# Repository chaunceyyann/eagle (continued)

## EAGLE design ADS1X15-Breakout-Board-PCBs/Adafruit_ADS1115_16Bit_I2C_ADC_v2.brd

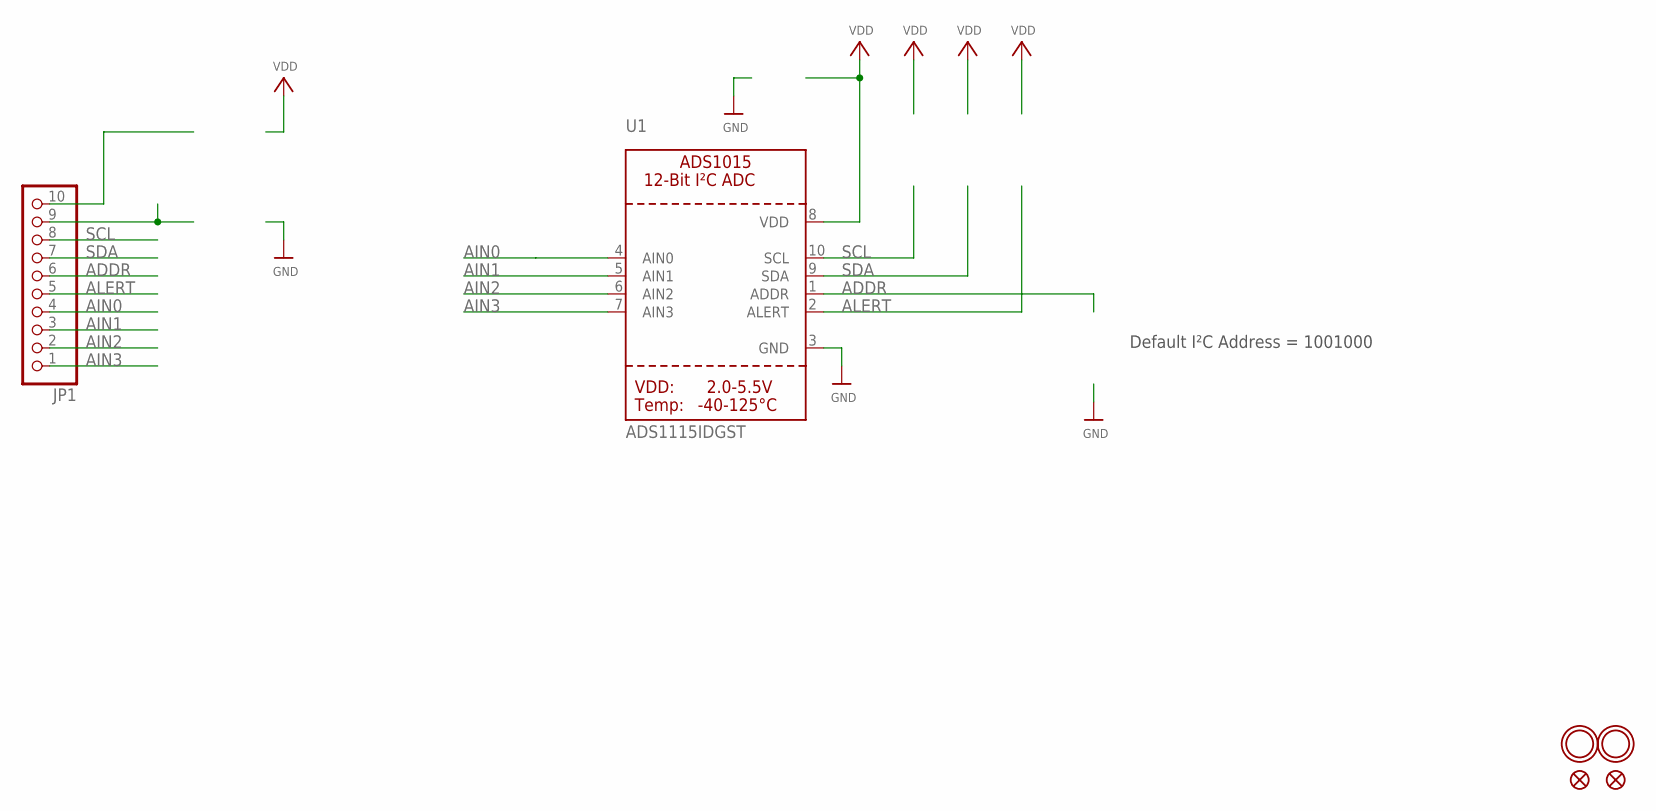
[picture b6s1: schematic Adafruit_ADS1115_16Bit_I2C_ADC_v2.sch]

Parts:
FID1, FID2: FIDUCIAL""; FIDUCIAL_1MM
JP1: HEADER-1X1070MIL; 1X10_ROUND70
U1: ADS1115IDGST; MSOP10
U$13, U$14: MOUNTINGHOLE2.5; MOUNTINGHOLE_2.5_PLATED

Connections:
ADDR: JP1.6, U1.1 (ADDR)
AIN0: JP1.4, U1.4 (AIN0)
AIN1: JP1.3, U1.5 (AIN1)
AIN2: JP1.2, U1.6 (AIN2)
AIN3: JP1.1, U1.7 (AIN3)
ALERT: JP1.5, U1.2 (ALERT)
GND: U1.3 (GND)
SCL: JP1.8, U1.10 (SCL)
SDA: JP1.7, U1.9 (SDA)
VDD: U1.8 (VDD)

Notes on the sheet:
Default I²C Address = 1001000

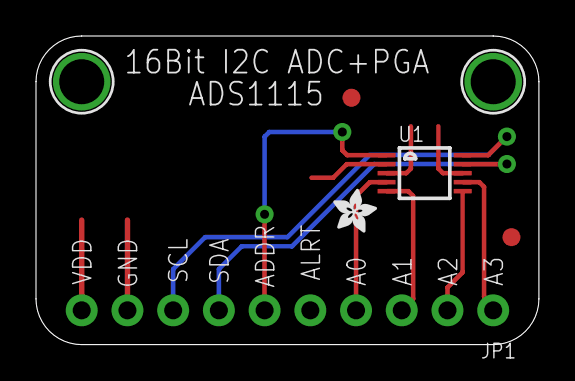
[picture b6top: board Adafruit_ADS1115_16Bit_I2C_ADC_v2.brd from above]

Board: 2 copper layers, 27.9 x 17.1 mm, 8 parts (1 on the bottom side), 8 nets.

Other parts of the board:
U$15: ADAFRUIT_TEXT_20MM
U$16: ADAFRUIT_2.5MM

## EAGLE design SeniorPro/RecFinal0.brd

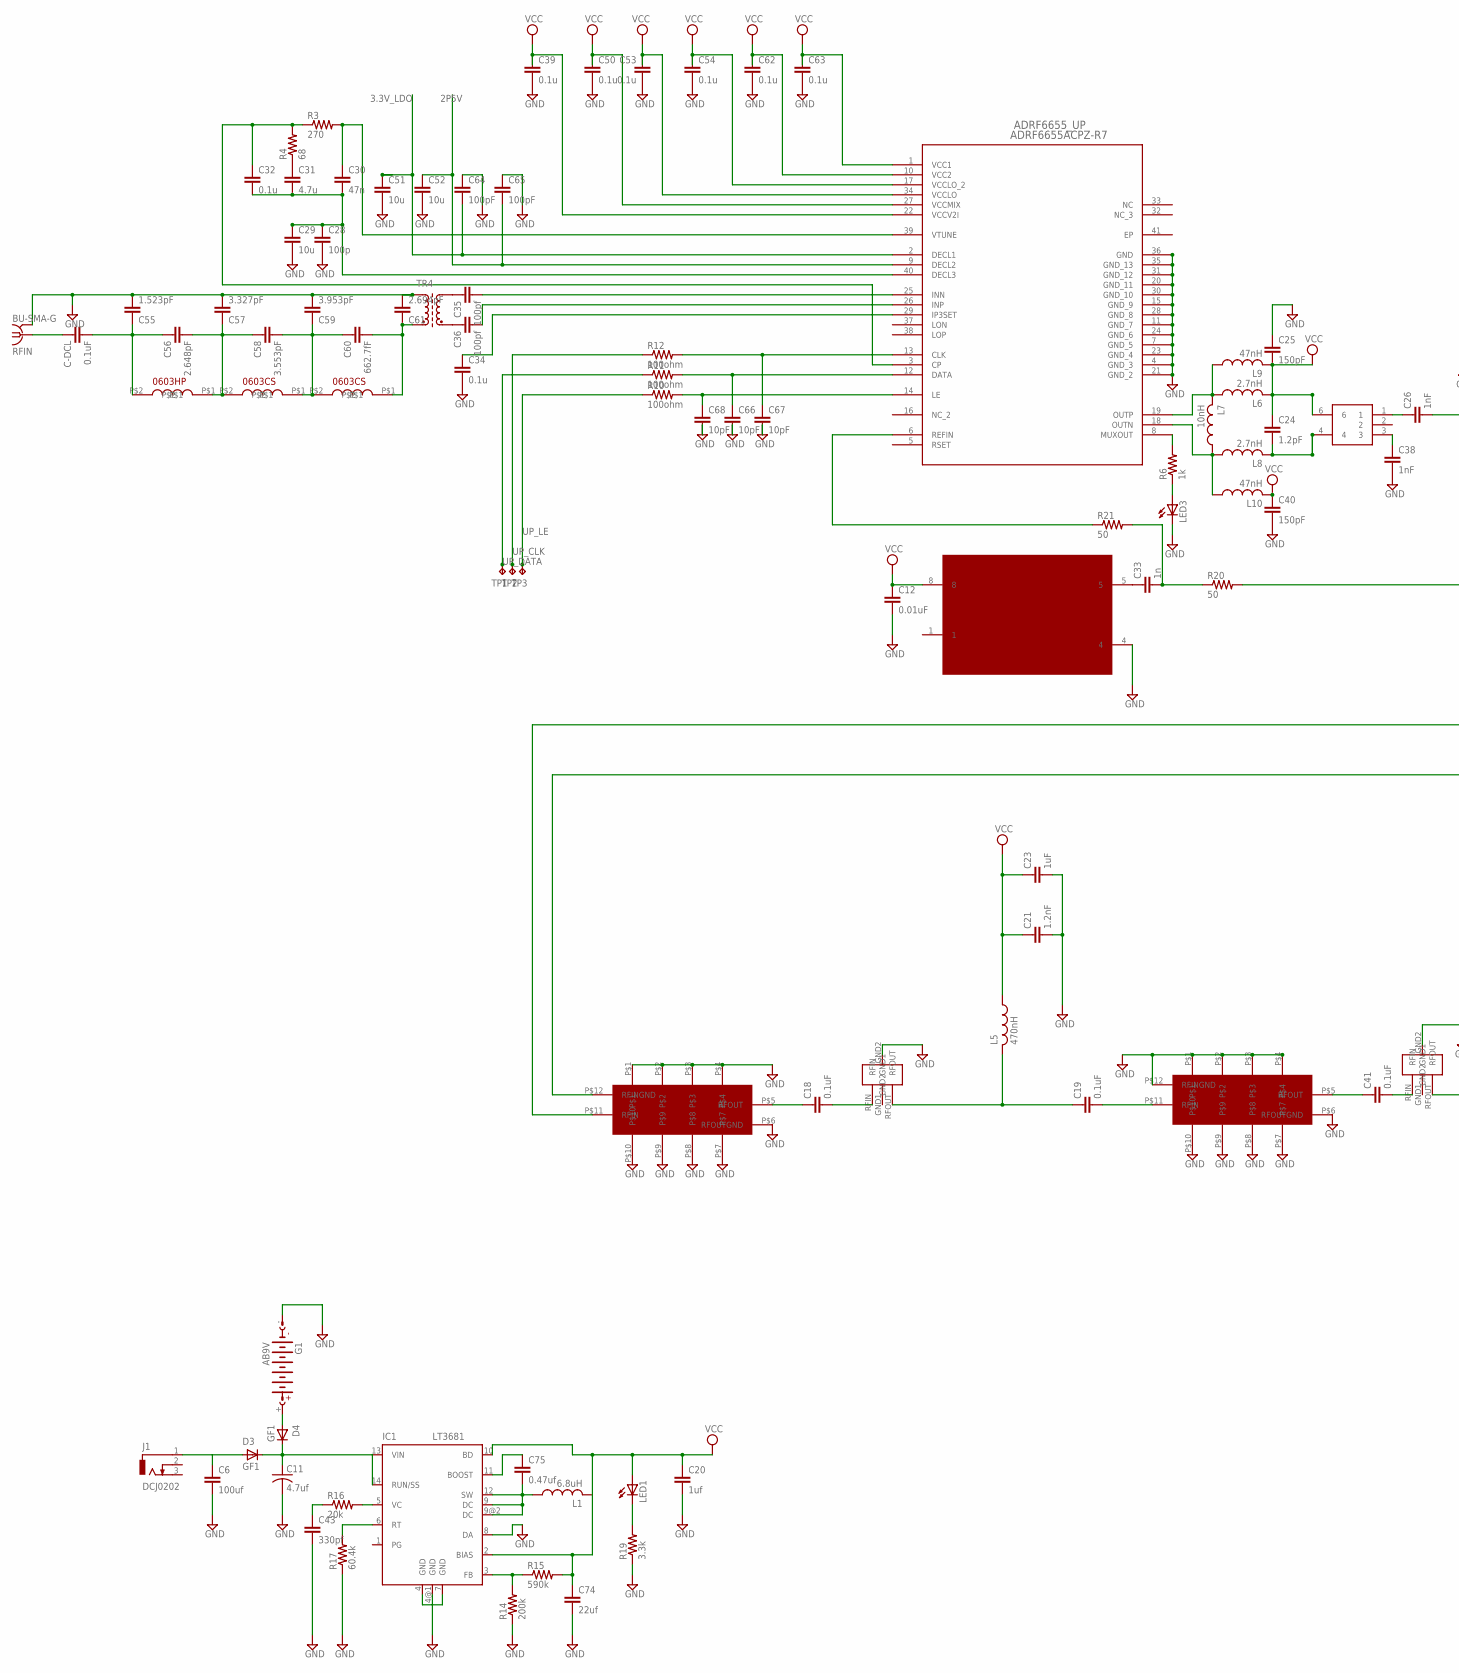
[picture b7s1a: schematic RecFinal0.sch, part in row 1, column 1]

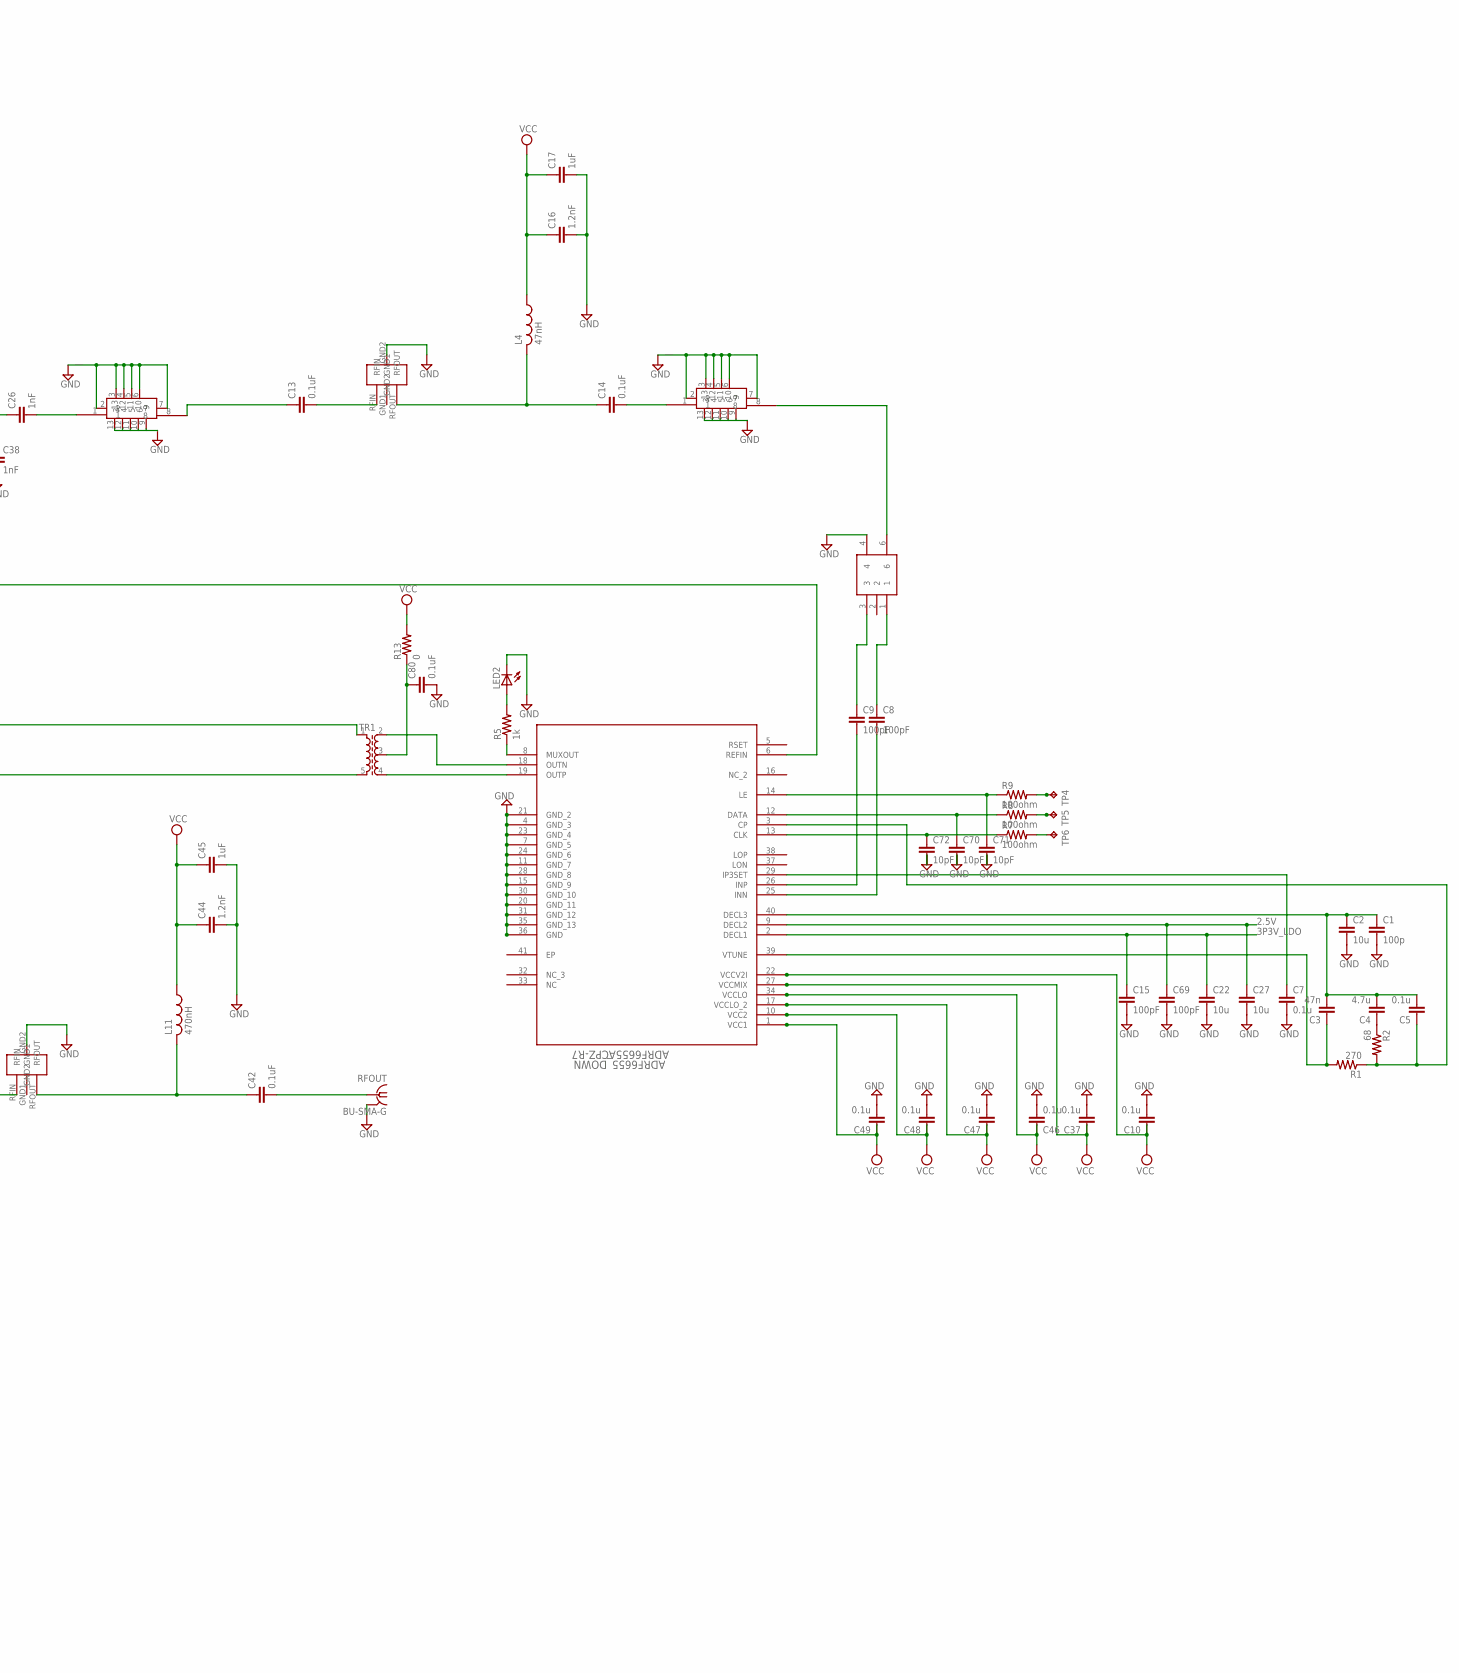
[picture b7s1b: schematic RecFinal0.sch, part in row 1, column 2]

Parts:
06CS9N5, 0603CS5N6: 0603CS
0603HP5N6: 0603HP
1401, 1402: SF2140A
ADRF6655_DOWN, ADRF6655_UP: ADRF6655ACPZ-R7; CP_40_1
C1, C28: 100p; C0603K
C2, C22, C27, C29, C51, C52: 10u; C0603K
C3, C30: 47n; C0603K
C4, C31: 4.7u; C0603K
C5, C7, C10, C32, C34, C37, C39, C46, C47, C48, C49, C50, C53, C54, C62, C63: 0.1u; C0603K
C6: 100uf; C0603K
C8, C9, C15, C64, C65, C69: 100pF; C0603K
C11: 4.7uf; C050-024X044
C12: 0.01uF; C0603K
C13, C14, C18, C19, C41, C42, C80: 0.1uF; C0603K
C16, C21, C44: 1.2nF; C0603K
C17, C23, C45: 1uF; C0603K
C20: 1uf; C0603K
C24: 1.2pF; C0603K
C25, C40: 150pF; C0603K
C26, C38: 1nF; C0603K
C33: 1n; C0603K
C35, C36: 100pf; C0603K
C43: 330pf; C0603K
C55: 1.523pF; C0603K
C56: 2.648pF; C0603K
C57: 3.327pF; C0603K
C58: 3.553pF; C0603K
C59: 3.953pF; C0603K
C60: 662.7fF; C0603K
C61: 2.694pF; C0603K
C66, C67, C68, C70, C71, C72: 10pF; C0603K
C74: 22uf; C0603K
C75: 0.47uf; C0603K
C-DCL: 0.1uF; C0603K
D3, D4: GF1; SMA-DO214AC
G1: AB9V
IC1: LT3681; DFN14-4X3DE
J1: DCJ0202
L1: 6.8uH; L2012C
L4, L9, L10: 47nH; L2012C
L5, L11: 470nH; L2012C
L6, L8: 2.7nH; L2012C
L7: 10nH; L2012C
LED1, LED2, LED3: LED_ESML0603; LED_SML0603
R1, R3: 270; R0603
R2, R4: 68; R0603
R5, R6: 1k; R0603
R7, R8, R9, R10, R11, R12: 100ohm; R0603
R13: 0; R0603
R14: 200k; R0603
R15: 590k; R0603
R16: 20k; R0603
R17: 60.4k; R0603
R19: 3.3k; R0603
R20, R21: 50; R0603
RFIN: BU-SMA-G
RFOUT: BU-SMA-G
T$2, T$3: CUSTOM_TRANSFORMER
TP1, TP2, TP3, TP4, TP5, TP6: TPPAD1-13; P1-13
TR1: SM-T4-2T; SM-T4
TR4: SM-T4
U$1: MXO45
U$2, U$4: RCFD1
U$3, U$5, U$6: ADL5320

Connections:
2.5V: ADRF6655_DOWN.9 (DECL2), C27.1, C69.1
2P5V: ADRF6655_UP.9 (DECL2), C52.1, C65.2
3.3V_LDO: ADRF6655_UP.2 (DECL1), C51.1, C64.2
3P3V_LDO: ADRF6655_DOWN.2 (DECL1), C15.1, C22.1
DOWN_CLK: R7.2, TP6.TP
DOWN_DATA: R8.2, TP5.TP
DOWN_LE: R9.2, TP4.TP
GND: 1401.P$1, 1401.P$2, 1401.P$3, 1401.P$4, 1401.P$6 (RFOUTGND), 1401.P$7, 1401.P$8, 1401.P$9, 1401.P$10, 1402.P$1, 1402.P$2, 1402.P$3, 1402.P$4, 1402.P$6 (RFOUTGND), 1402.P$7, 1402.P$8, 1402.P$9, 1402.P$10, 1402.P$12 (RFINGND), ADRF6655_DOWN.4 (GND_3), ADRF6655_DOWN.7 (GND_5), ADRF6655_DOWN.11 (GND_7), ADRF6655_DOWN.15 (GND_9), ADRF6655_DOWN.20 (GND_11), ADRF6655_DOWN.21 (GND_2), ADRF6655_DOWN.23 (GND_4), ADRF6655_DOWN.24 (GND_6), ADRF6655_DOWN.28 (GND_8), ADRF6655_DOWN.30 (GND_10), ADRF6655_DOWN.31 (GND_12), ADRF6655_DOWN.35 (GND_13), ADRF6655_DOWN.36 (GND), ADRF6655_UP.4 (GND_3), ADRF6655_UP.7 (GND_5), ADRF6655_UP.11 (GND_7), ADRF6655_UP.15 (GND_9), ADRF6655_UP.20 (GND_11), ADRF6655_UP.21 (GND_2), ADRF6655_UP.23 (GND_4), ADRF6655_UP.24 (GND_6), ADRF6655_UP.28 (GND_8), ADRF6655_UP.30 (GND_10), ADRF6655_UP.31 (GND_12), ADRF6655_UP.35 (GND_13), ADRF6655_UP.36 (GND), C1.2, C2.2, C6.2, C7.2, C10.2, C11.2, C12.2, C15.2, C16.2, C17.2, C20.2, C21.2, C22.2, C23.2, C25.1, C27.2, C28.2, C29.2, C34.2, C37.2, C38.2, C39.2, C40.2, C43.2, C44.2, C45.2, C46.2, C47.2, C48.2, C49.2, C50.2, C51.2, C52.2, C53.2, C54.2, C55.2, C57.2, C59.2, C61.2, C62.2, C63.2, C64.1, C65.1, C66.2, C67.2, C68.2, C69.2, C70.2, C71.2, C72.2, C74.2, C80.2, G1.-, IC1.4 (GND), IC1.4@1 (GND), IC1.7 (GND), IC1.8 (DA), LED2.C, LED3.C, R14.1, R17.1, R19.1, RFIN.2, RFIN.3 (2), RFIN.4 (2), RFIN.5 (2), RFOUT.2, RFOUT.3 (2), RFOUT.4 (2), RFOUT.5 (2), T$3.4, TR4.1 (A1), U$1.4, U$2.2, U$2.3, U$2.4, U$2.5, U$2.6, U$2.7, U$2.9, U$2.10, U$2.11, U$2.12, U$2.13, U$4.2, U$4.3, U$4.4, U$4.5, U$4.6, U$4.7, U$4.9, U$4.10, U$4.11, U$4.12, U$4.13, U$5.GND2
unnamed: ADRF6655_UP.39 (VTUNE), C30.1, R3.2
unnamed: ADRF6655_DOWN.39 (VTUNE), C3.1, R1.2
unnamed: ADRF6655_DOWN.40 (DECL3), C1.1, C2.1, C3.2, C4.2, C5.2
unnamed: ADRF6655_DOWN.6 (REFIN), R20.2
unnamed: ADRF6655_DOWN.14 (LE), C71.1, R9.1
unnamed: ADRF6655_DOWN.12 (DATA), C70.1, R8.1
unnamed: ADRF6655_DOWN.29 (IP3SET), C7.1
unnamed: ADRF6655_DOWN.26 (INP), C9.2
unnamed: ADRF6655_DOWN.25 (INN), C8.2
unnamed: ADRF6655_DOWN.18 (OUTN), TR1.2
unnamed: ADRF6655_DOWN.19 (OUTP), TR1.4
unnamed: C38.1, T$2.3
unnamed: ADRF6655_UP.3 (CP), C32.1, R3.1, R4.2
unnamed: ADRF6655_UP.40 (DECL3), C28.1, C29.1, C30.2, C31.2, C32.2
unnamed: C33.1, U$1.5
unnamed: C26.2, U$2.1
unnamed: ADRF6655_UP.13 (CLK), C67.1, R12.2
unnamed: ADRF6655_UP.29 (IP3SET), C34.1
unnamed: ADRF6655_UP.25 (INN), C35.2
unnamed: ADRF6655_UP.26 (INP), C36.2
unnamed: C-DCL.1, RFIN.1
unnamed: 0603HP5N6.P$2, C55.1, C56.1, C-DCL.2
unnamed: C41.2, U$5.RFIN
unnamed: 06CS9N5.P$1, C60.2, C61.1, TR4.2 (E1)
unnamed: 06CS9N5.P$2, 0603CS5N6.P$1, C58.2, C59.1, C60.1
unnamed: 0603CS5N6.P$2, 0603HP5N6.P$1, C56.2, C57.1, C58.1
unnamed: C13.1, U$2.8
unnamed: ADRF6655_UP.12 (DATA), C66.1, R11.2
unnamed: C31.1, R4.1
unnamed: C4.1, R2.1
unnamed: C14.1, L4.2, U$3.RFOUT
unnamed: ADRF6655_UP.8 (MUXOUT), R6.2
unnamed: LED3.A, R6.1
unnamed: C14.2, U$4.1
unnamed: IC1.5 (VC), R16.2
unnamed: ADRF6655_DOWN.3 (CP), C5.1, R1.1, R2.2
unnamed: C19.1, L5.2, U$6.RFOUT
unnamed: 1401.P$5 (RFOUT), C18.1
unnamed: 1402.P$11 (RFIN), C19.2
unnamed: ADRF6655_UP.19 (OUTP), L6.1, L7.2, L9.1
unnamed: ADRF6655_UP.18 (OUTN), L7.1, L8.1, L10.1
unnamed: ADRF6655_DOWN.13 (CLK), C72.1, R7.1
unnamed: T$3.6, U$4.8
unnamed: C24.2, L8.2, T$2.4
unnamed: ADRF6655_UP.6 (REFIN), R21.1
unnamed: C33.2, R20.1, R21.2
unnamed: C80.1, R13.1, TR1.3
unnamed: 1401.P$12 (RFINGND), TR1.5
unnamed: 1401.P$11 (RFIN), TR1.1
unnamed: C18.2, U$6.RFIN
unnamed: C42.1, L11.2, U$5.RFOUT
unnamed: 1402.P$5 (RFOUT), C41.1
unnamed: C42.2, RFOUT.1
unnamed: C9.1, T$3.3
unnamed: C8.1, T$3.1
unnamed: C35.1, TR4.5 (A2)
unnamed: C36.1, TR4.4 (E2)
unnamed: ADRF6655_UP.14 (LE), C68.1, R10.2
unnamed: ADRF6655_DOWN.8 (MUXOUT), R5.1
unnamed: C13.2, U$3.RFIN
unnamed: C26.1, T$2.1
unnamed: IC1.6 (RT), R17.2
unnamed: C43.1, R16.1
unnamed: IC1.3 (FB), R14.2, R15.1
unnamed: C75.1, IC1.11 (BOOST)
unnamed: LED2.A, R5.2
unnamed: C11.1, D3.K (C), D4.K (C), IC1.13 (VIN), IC1.14 (RUN/SS)
unnamed: D4.A, G1.+
unnamed: C75.2, IC1.9 (DC), IC1.9@2 (DC), IC1.12 (SW), L1.1
unnamed: LED1.C, R19.2
unnamed: C6.1, D3.A, J1.1
UP_CLK: R12.1, TP2.TP
UP_DATA: R11.1, TP1.TP
UP_LE: R10.1, TP3.TP
VCC: ADRF6655_DOWN.1 (VCC1), ADRF6655_DOWN.10 (VCC2), ADRF6655_DOWN.17 (VCCLO_2), ADRF6655_DOWN.22 (VCCV2I), ADRF6655_DOWN.27 (VCCMIX), ADRF6655_DOWN.34 (VCCLO), ADRF6655_UP.1 (VCC1), ADRF6655_UP.10 (VCC2), ADRF6655_UP.17 (VCCLO_2), ADRF6655_UP.22 (VCCV2I), ADRF6655_UP.27 (VCCMIX), ADRF6655_UP.34 (VCCLO), C10.1, C12.1, C16.1, C17.1, C20.1, C21.1, C23.1, C24.1, C25.2, C37.1, C39.1, C40.1, C44.1, C45.1, C46.1, C47.1, C48.1, C49.1, C50.1, C53.1, C54.1, C62.1, C63.1, C74.1, IC1.2 (BIAS), IC1.10 (BD), L1.2, L4.1, L5.1, L6.2, L9.2, L10.2, L11.1, LED1.A, R13.2, R15.2, T$2.6, U$1.8

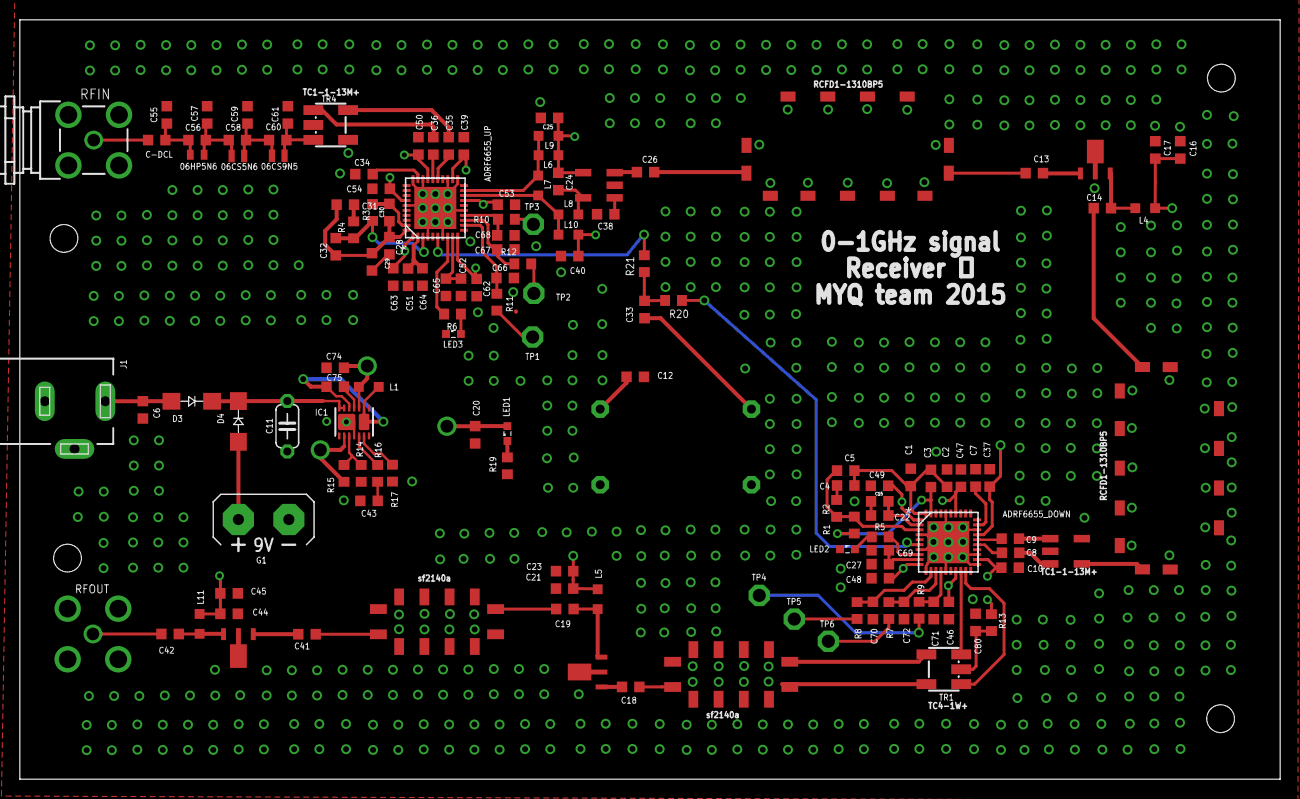
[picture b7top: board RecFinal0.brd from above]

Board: 4 copper layers, 127.0 x 76.5 mm, 138 parts (1 on the bottom side), 83 nets.

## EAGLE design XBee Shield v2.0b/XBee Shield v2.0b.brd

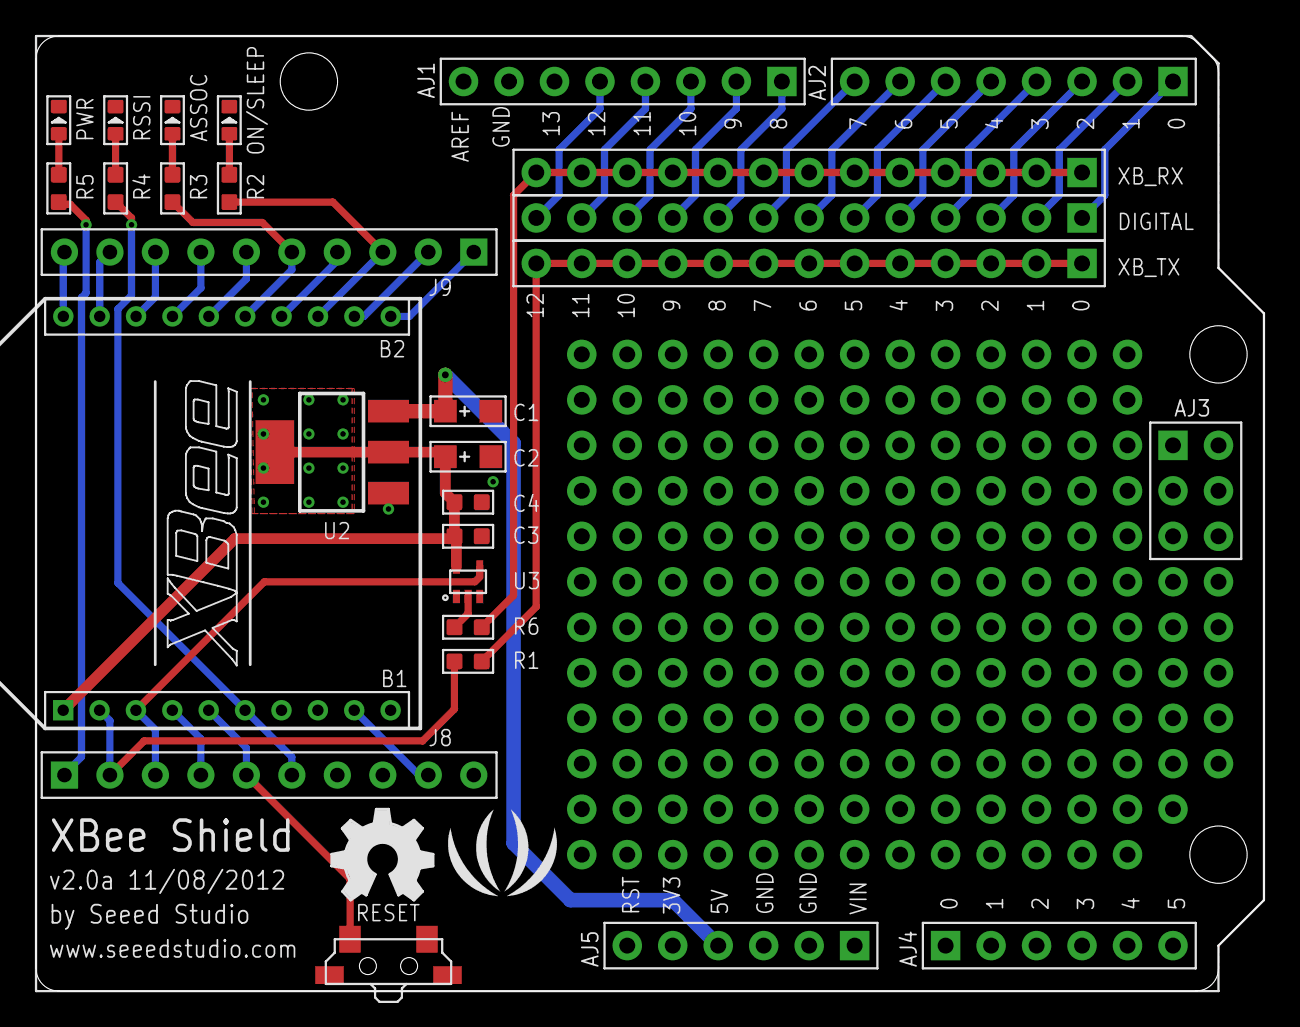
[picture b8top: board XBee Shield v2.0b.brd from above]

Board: 2 copper layers, 68.6 x 53.3 mm, 26 parts (0 on the bottom side), 40 nets.

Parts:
ASSOC: GREEN; LED-0603
C1, C2: 10uF_16V; AVX-A
C3, C4: 100nF; C0603
DIGITAL: 13P-2.54
J8, J9: DNP; CK1X10
ON/SLEEP: GREEN; LED-0603
PWR: GREEN; LED-0603
R1: 33; R0603
R2, R3, R4, R5, R6: 1k; R0603
RESET: FOR_TEST_ALBERT_V6_4P-SMD-7X3.5X3.5
RSSI: RED; LED-0603
U1: ARDUINO-W/O-SILK
U2: CJT1117-3.3; SOT-223
U3: SN74LVC1G125DCKR; SOT353
U$2: LOGO_SILK
U$3: OSHW_FILLX200_NOTEXT
XBEE: XBEEEXT; XBEE_PLUG
XB_RX: 13P-2.54
XB_TX: 13P-2.54

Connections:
3V3: C2.+, C3.1, C4.2, U2.2, U2.TER, U3.5, XBEE.1
5V: C1.+, U1.26, U2.3
ASSOC: J9.5, R3.2, XBEE.15
D0: DIGITAL.1, U1.1
D1: DIGITAL.2, U1.2
D2: DIGITAL.3, U1.3
D3: DIGITAL.4, U1.4
D4: DIGITAL.5, U1.5
D5: DIGITAL.6, U1.6
D6: DIGITAL.7, U1.7
D7: DIGITAL.8, U1.8
D8: DIGITAL.9, U1.9
D9: DIGITAL.10, U1.10
D10: DIGITAL.11, U1.11
D11: DIGITAL.12, U1.12
D12: DIGITAL.13, U1.13
GND: ASSOC.-, C1.-, C2.-, C3.2, C4.1, J8.10, ON/SLEEP.-, PWR.-, RESET.2, RESET.S1, RESET.S2, RSSI.-, U1.15, U1.24, U1.25, U2.1, U3.1, U3.3, XBEE.10
unnamed: ON/SLEEP.+, R2.1
unnamed: ASSOC.+, R3.1
unnamed: R4.1, RSSI.+
unnamed: PWR.+, R5.1
unnamed: R6.2, U3.2
ON/SLEEP: J9.3, R2.2, XBEE.13
RSSI: J8.6, R4.2, XBEE.6
RST: J8.5, RESET.1, XBEE.5
RX: R6.1, XB_RX.1, XB_RX.2, XB_RX.3, XB_RX.4, XB_RX.5, XB_RX.6, XB_RX.7, XB_RX.8, XB_RX.9, XB_RX.10, XB_RX.11, XB_RX.12, XB_RX.13
TX: R1.1, XB_TX.1, XB_TX.2, XB_TX.3, XB_TX.4, XB_TX.5, XB_TX.6, XB_TX.7, XB_TX.8, XB_TX.9, XB_TX.10, XB_TX.11, XB_TX.12, XB_TX.13
XB4: J8.4, XBEE.4
XB11: J9.1, XBEE.11
XB14: J9.4, XBEE.14
XB17: J9.7, XBEE.17
XB18: J9.8, XBEE.18
XB19: J9.9, XBEE.19
XB20: J9.10, XBEE.20
XBEE_DTR: J8.9, XBEE.9
X_3V3: J8.1, R5.2
X_CTS: J9.2, XBEE.12
X_RTS: J9.6, XBEE.16
X_RX: J8.3, U3.4, XBEE.3
X_TXD: J8.2, R1.2, XBEE.2

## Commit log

2015-11-17 Initial
2015-11-17 Pulled from work desktop
2015-11-25 Grab everything on ChauncityBass
2016-02-05 Added models from Eagle 7.5
2016-03-22 Updated 323 project and O2 project
2016-03-26 Modified the O2 circuits and changed the layout.
2016-03-26 Modified the sch and layout again. Ready for deliver
2016-12-15 Clean Up
